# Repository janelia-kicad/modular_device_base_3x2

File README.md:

- [Repository Information](#org2d3cf65)
  - [Description](#org1d457c5)
- [Images](#orgf7fc59b)
- [Schematic](#org84fa638)
- [Gerbers](#org0e5c931)
- [Bill of Materials](#orgdca82e4)
  - [PCB Parts](#org3aed68a)
  - [Supplemental Parts](#orgb3f0c54)
  - [Vendor Parts Lists](#orgffdd84b)
- [Supplemental Documentation](#org0fd8fc3)
  - [Assembly Instructions](#org74b49ca)

# Repository Information

-   **Name:** modular\_device\_base\_3x2
-   **Version:** 1.2
-   **License:** Open-Source Hardware
-   **URL:** <https://github.com/janelia-kicad/modular_device_base_3x2>
-   **Author:** Peter Polidoro
-   **Email:** peter@polidoro.io

## Description

This board is the base of 3x2 format modular devices. It is a breakout board for the microprocessor, with connections for power, communication, and top boards.

# Images

# Schematic

[./schematic/modular\_device\_base\_3x2.pdf](./schematic/modular_device_base_3x2.pdf)

# Gerbers

Send gerbers zip file to your favorite PCB manufacturer for fabrication.

[./gerbers/modular\_device\_base\_3x2\_v1.2.zip](./gerbers/modular_device_base_3x2_v1.2.zip)

# Bill of Materials

## PCB Parts

| Item | Reference(s)         | Quantity | PartNumber          | Vendor  | Description                                           |
|---- |-------------------- |-------- |------------------- |------- |----------------------------------------------------- |
| 1    | C1 C2 C3 C4 C5       | 5        | 445-4536-1-ND       | digikey | CAP CER 10UF 50V 10% X7S 1210                         |
| 2    | C6                   | 1        | 399-13229-1-ND      | digikey | CAP CER 0.1UF 100V X7R 1210                           |
| 3    | D1 D2                | 2        | LSM115JE3/TR13CT-ND | digikey | DIODE SCHOTTKY 15V 1A DO214BA                         |
| 4    | D3 D4 D5 D6 D7 D8 D9 | 7        | 568-11697-1-ND      | digikey | DIODE SCHOTTKY 45V 10A CFP15                          |
| 5    | L1                   | 1        | 350-1712-ND         | digikey | LED 2MM 5V RT ANGLE RED PCMNT                         |
| 6    | L2                   | 1        | 350-1717-ND         | digikey | LED 2MM 5V RT ANGLE GREEN PCMNT                       |
| 7    | L3                   | 1        | 350-1719-ND         | digikey | LED 2MM 5V RT ANGLE YELLOW PCMNT                      |
| 8    | MDB1                 | 2        | S7049-ND            | digikey | 16 Position Header Through Hole Female Socket         |
| 9    | MH1 MH2 MH3 MH4      | 4        | 36-2027-ND          | digikey | Round Standoff Threaded 4-40 Aluminum 0.500in 0.187in |
| 10   | P1                   | 1        | CP-063BH-ND         | digikey | CONN PWR JACK DC 2.5X5.5 8A T/H                       |
| 11   | P2                   | 1        | ACX1655-ND          | digikey | CONN BNC JACK R/A 75 OHM PCB                          |
| 12   | P3 P5                | 2        | A100890CT-ND        | digikey | CONN HEADER 3POS R/A SMD GOLD                         |
| 13   | P4 P6                | 2        | A100903CT-ND        | digikey | CONN HEADER 2POS R/A SMD GOLD                         |
| 14   | P7                   | 1        | 732-5336-ND         | digikey | CONN HEADER 3 POS RA 2.54                             |
| 15   | P8                   | 1        | SAM10781-ND         | digikey | CONN HEADER 2POS .100in SNGL SMD                      |
| 16   | R1                   | 1        | P6.19KAACT-ND       | digikey | RES SMD 6.19K OHM 1% 1/2W 1210                        |
| 17   | REG1                 | 1        | 945-1395-5-ND       | digikey | CONV DC/DC 1A 5V OUT SIP VERT                         |
| 18   | SW1                  | 1        | CKN1860CT-ND        | digikey | SWITCH TACTILE SPST-NO 1VA 32V                        |
| 19   | TEENSY1              | 1        | 1568-1231-ND        | digikey | DEV TEENSY 3.2 13736                                  |
| 20   | U1                   | 1        | MAX6817EUT+TCT-ND   | digikey | IC DEBOUNCER SWITCH DUAL SOT23-6                      |

## Supplemental Parts

| Item | Quantity | PartNumber    | Vendor  | Description                                                              |
|---- |-------- |------------- |------- |------------------------------------------------------------------------ |
| 1    | 1        | EPS594-ND     | digikey | 30 WATT DESKTOP POWER SUPPLY 24V                                         |
| 2    | 1        | 993-1037-ND   | digikey | CORD 3COND NEMA PLUG 320-C5                                              |
| 3    | 1        | A106625CT-ND  | digikey | 14 Positions Header Unshrouded Breakaway Connector 0.100in 2 row SMD     |
| 4    | 2        | S1011EC-24-ND | digikey | 24 Positions Header Unshrouded Breakaway Connector 0.100in 1 row Through |
| 5    | 1        | S9001-ND      | digikey | CONN JUMPER SHORTING GOLD FLASH                                          |
| 6    | 1        | AE10342-ND    | digikey | CABLE USB-A TO MICRO USB-B 2M                                            |

## Vendor Parts Lists

[./bom/digikey\_parts.csv](./bom/digikey_parts.csv)

[./bom/supplemental\_digikey\_parts.csv](./bom/supplemental_digikey_parts.csv)

# Supplemental Documentation

## Assembly Instructions

-   Cut the bottom trace on the Teensy board that connects the 5V pads according to these instructions <https://www.pjrc.com/teensy/external_power.html>.
-   Solder through hole header pins into every Teensy 0.1 inch header hole.
-   Solder surface mount header pins onto the bottom of the Teensy making sure they are properly aligned.
-   Solder surface mount and through hole components onto the pcb.
-   Solder the Teensy into the pcb making sure it is properly aligned.
-   Connect header jumper to RED LED enable pins.

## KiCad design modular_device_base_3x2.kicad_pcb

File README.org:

# Created 2018-05-18 Fri 09:40
#+OPTIONS: title:nil author:nil email:nil toc:t |:t ^:nil
* Repository Information

- Name :: modular_device_base_3x2
- Version :: 1.2
- License :: Open-Source Hardware
- URL :: https://github.com/janelia-kicad/modular_device_base_3x2
- Author :: Peter Polidoro
- Email :: peter@polidoro.io

** Description

This board is the base of 3x2 format modular devices. It is a breakout board
for the microprocessor, with connections for power, communication, and top
boards.

* Images

[[file:./images/top.png]]

[[file:./images/bottom.png]]

* Schematic

[[file:./schematic/modular_device_base_3x2.pdf][./schematic/modular_device_base_3x2.pdf]]

[[file:./schematic/images/schematic00.png]]

* Gerbers

Send gerbers zip file to your favorite PCB manufacturer for fabrication.

[[file:./gerbers/modular_device_base_3x2_v1.2.zip][./gerbers/modular_device_base_3x2_v1.2.zip]]

[[file:./gerbers/images/gerbers00.png]]

[[file:./gerbers/images/gerbers01.png]]

* Bill of Materials

** PCB Parts

| Item | Reference(s)         | Quantity | PartNumber          | Vendor  | Description                                           |
|------+----------------------+----------+---------------------+---------+-------------------------------------------------------|
|    1 | C1 C2 C3 C4 C5       |        5 | 445-4536-1-ND       | digikey | CAP CER 10UF 50V 10% X7S 1210                         |
|    2 | C6                   |        1 | 399-13229-1-ND      | digikey | CAP CER 0.1UF 100V X7R 1210                           |
|    3 | D1 D2                |        2 | LSM115JE3/TR13CT-ND | digikey | DIODE SCHOTTKY 15V 1A DO214BA                         |
|    4 | D3 D4 D5 D6 D7 D8 D9 |        7 | 568-11697-1-ND      | digikey | DIODE SCHOTTKY 45V 10A CFP15                          |
|    5 | L1                   |        1 | 350-1712-ND         | digikey | LED 2MM 5V RT ANGLE RED PCMNT                         |
|    6 | L2                   |        1 | 350-1717-ND         | digikey | LED 2MM 5V RT ANGLE GREEN PCMNT                       |
|    7 | L3                   |        1 | 350-1719-ND         | digikey | LED 2MM 5V RT ANGLE YELLOW PCMNT                      |
|    8 | MDB1                 |        2 | S7049-ND            | digikey | 16 Position Header Through Hole Female Socket         |
|    9 | MH1 MH2 MH3 MH4      |        4 | 36-2027-ND          | digikey | Round Standoff Threaded 4-40 Aluminum 0.500in 0.187in |
|   10 | P1                   |        1 | CP-063BH-ND         | digikey | CONN PWR JACK DC 2.5X5.5 8A T/H                       |
|   11 | P2                   |        1 | ACX1655-ND          | digikey | CONN BNC JACK R/A 75 OHM PCB                          |
|   12 | P3 P5                |        2 | A100890CT-ND        | digikey | CONN HEADER 3POS R/A SMD GOLD                         |
|   13 | P4 P6                |        2 | A100903CT-ND        | digikey | CONN HEADER 2POS R/A SMD GOLD                         |
|   14 | P7                   |        1 | 732-5336-ND         | digikey | CONN HEADER 3 POS RA 2.54                             |
|   15 | P8                   |        1 | SAM10781-ND         | digikey | CONN HEADER 2POS .100in SNGL SMD                      |
|   16 | R1                   |        1 | P6.19KAACT-ND       | digikey | RES SMD 6.19K OHM 1% 1/2W 1210                        |
|   17 | REG1                 |        1 | 945-1395-5-ND       | digikey | CONV DC/DC 1A 5V OUT SIP VERT                         |
|   18 | SW1                  |        1 | CKN1860CT-ND        | digikey | SWITCH TACTILE SPST-NO 1VA 32V                        |
|   19 | TEENSY1              |        1 | 1568-1231-ND        | digikey | DEV TEENSY 3.2 13736                                  |
|   20 | U1                   |        1 | MAX6817EUT+TCT-ND   | digikey | IC DEBOUNCER SWITCH DUAL SOT23-6                      |

** Supplemental Parts

| Item | Quantity | PartNumber    | Vendor  | Description                                                              |
|------+----------+---------------+---------+--------------------------------------------------------------------------|
|    1 |        1 | EPS594-ND     | digikey | 30 WATT DESKTOP POWER SUPPLY 24V                                         |
|    2 |        1 | 993-1037-ND   | digikey | CORD 3COND NEMA PLUG 320-C5                                              |
|    3 |        1 | A106625CT-ND  | digikey | 14 Positions Header Unshrouded Breakaway Connector 0.100in 2 row SMD     |
|    4 |        2 | S1011EC-24-ND | digikey | 24 Positions Header Unshrouded Breakaway Connector 0.100in 1 row Through |
|    5 |        1 | S9001-ND      | digikey | CONN JUMPER SHORTING GOLD FLASH                                          |
|    6 |        1 | AE10342-ND    | digikey | CABLE USB-A TO MICRO USB-B 2M                                            |

** Vendor Parts Lists

[[file:./bom/digikey_parts.csv][./bom/digikey_parts.csv]]

[[file:./bom/supplemental_digikey_parts.csv][./bom/supplemental_digikey_parts.csv]]

* Supplemental Documentation

** Assembly Instructions

- Cut the bottom trace on the Teensy board that connects the 5V pads according
  to these instructions [[https://www.pjrc.com/teensy/external_power.html]].
- Solder through hole header pins into every Teensy 0.1 inch header hole.
- Solder surface mount header pins onto the bottom of the Teensy making sure
  they are properly aligned.
- Solder surface mount and through hole components onto the pcb.
- Solder the Teensy into the pcb making sure it is properly aligned.
- Connect header jumper to RED LED enable pins.

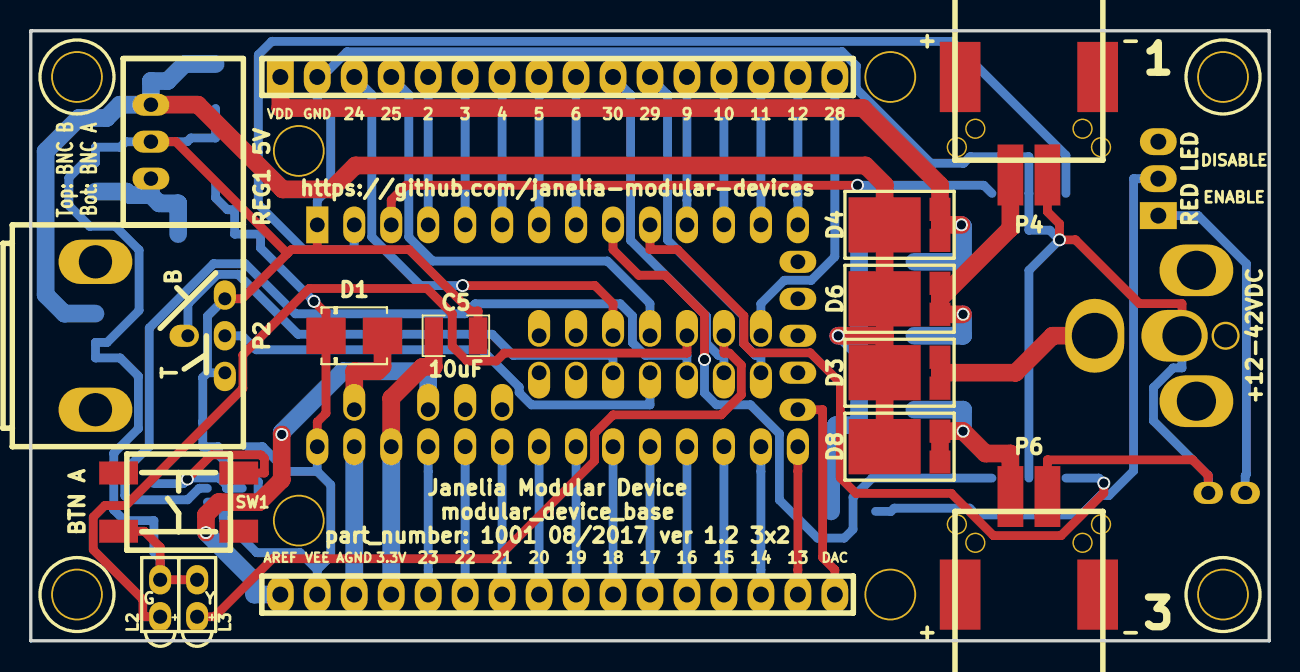
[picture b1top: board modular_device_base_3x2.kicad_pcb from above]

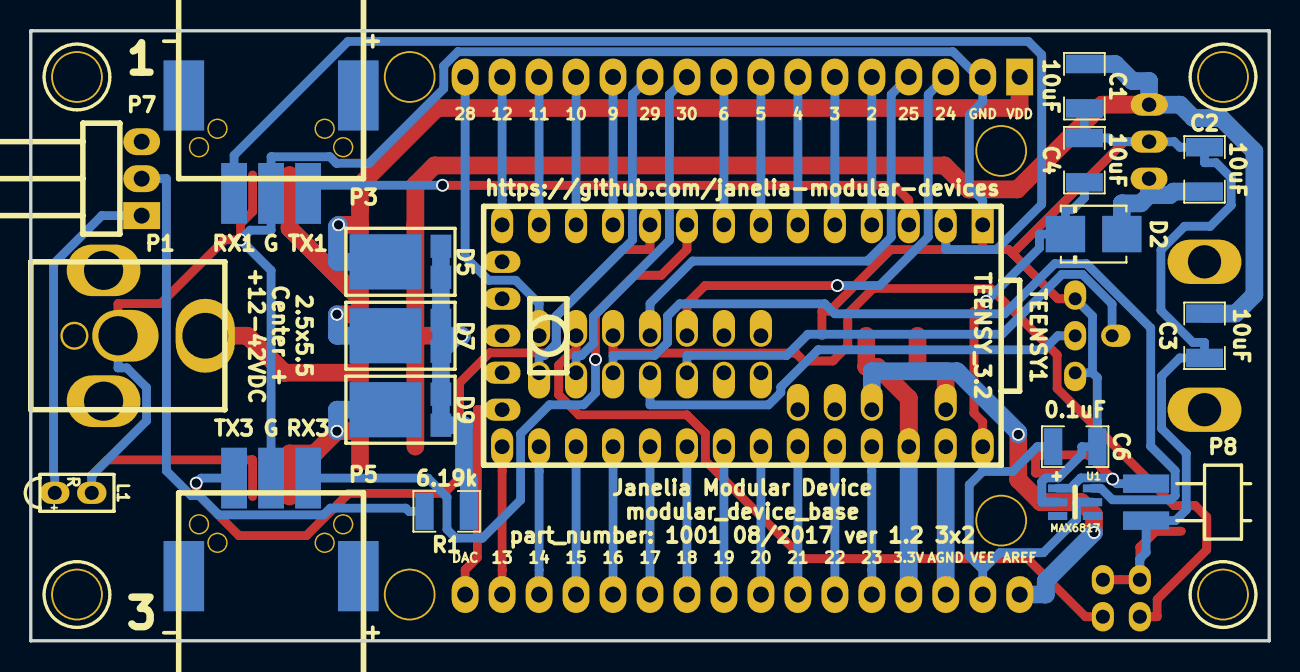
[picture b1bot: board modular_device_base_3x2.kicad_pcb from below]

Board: 2 copper layers, 85.1 x 41.9 mm, 36 parts (18 on the bottom side), 50 nets.

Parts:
C1, C2, C3, C4, C5: 10uF; SM1210
C6: 0.1uF; SM1210
D1, D2: diode_schottky_15V_1A; DO-214BA
D3, D4, D5, D6, D7, D8, D9: diode_schottky_45V_10A; CFP15
L1: LED_5V_RED_RA; LED_555-2XXX
L2: LED_5V_GRN_RA; LED_555-2XXX
L3: LED_5V_YEL_RA; LED_555-2XXX
MDB1: MODULAR_DEVICE_BASE_3x2_FEMALE; MODULAR_DEVICE_BASE_3X2_FEMALE
MH1, MH2, MH3, MH4: MNT_HOLE; MOUNTING_HOLE_4-40
P1: PWR_JACK_2.5x5.5; DCJACK_2PIN_HIGHCURRENT
P2: BNC_DOUBLE_RA; BNC_DOUBLE
P3, P5: HEADER_01X03_SMD_RA; Header_3_Pin_SMD_RA
P4, P6: HEADER_01X02_SMD_RA; Header_2_Pin_SMD_RA
P7: HEADER_01X03_RA; Header_3_Pin_RA
P8: HEADER_01X02_SMD_RA_UNSHR; Header_2_Pin_SMD_RA_UNSHR
R1: 6.19k; SM1210
REG1: CONV_DC_DC_5V_1A; DC_DC_CONV_R78C
SW1: KT_SWITCH
TEENSY1: TEENSY_3.2
U1: MAX6817

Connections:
+5V: C2.1, D2.2, REG1.3
/3V3: C5.1, MDB1.3V3, TEENSY1.3V3
/AGND: MDB1.AGND, TEENSY1.AGND
/AREF: MDB1.AREF, TEENSY1.AREF
/BNC_A: P2.1, TEENSY1.33
/BNC_B: P2.3, TEENSY1.32
/BTN_A: P8.1, SW1.2, U1.1
/BTN_A_D: TEENSY1.31, U1.6
/D2: MDB1.2, TEENSY1.2
/D3: MDB1.3, TEENSY1.3
/D4: MDB1.4, TEENSY1.4
/D5: MDB1.5, TEENSY1.5
/D6: MDB1.6, TEENSY1.6
/D9: MDB1.9, TEENSY1.9
/D10: MDB1.10, TEENSY1.10
/D11: MDB1.11, TEENSY1.11
/D12: MDB1.12, TEENSY1.12
/D13: MDB1.13, TEENSY1.13
/D14: MDB1.14, TEENSY1.14
/D15: MDB1.15, TEENSY1.15
/D16: MDB1.16, TEENSY1.16
/D17: MDB1.17, TEENSY1.17
/D18: MDB1.18, TEENSY1.18
/D19: MDB1.19, TEENSY1.19
/D20: MDB1.20, TEENSY1.20
/D21: MDB1.21, TEENSY1.21
/D22: MDB1.22, TEENSY1.22
/D23: MDB1.23, TEENSY1.23
/D24: MDB1.24, TEENSY1.24
/D25: MDB1.25, TEENSY1.25
/D28: MDB1.28, TEENSY1.28
/D29: MDB1.29, TEENSY1.29
/D30: MDB1.30, TEENSY1.30
/DAC: MDB1.DAC, TEENSY1.DAC
/LED_GRN: L2.1, TEENSY1.26
/LED_YEL: L3.1, TEENSY1.27
/RX1: P3.1, TEENSY1.0
/RX3: P5.1, TEENSY1.7
/TX1: P3.3, TEENSY1.1
/TX3: P5.3, TEENSY1.8
/V_USB: D1.2, TEENSY1.V_U
GND: C1.2, C2.2, C3.2, C4.2, C5.2, C6.2, L1.2, L2.2, L3.2, MDB1.GND, P1.2, P2.2, P2.4, P3.2, P4.2, P5.2, P6.1, P8.2, REG1.2, SW1.3, TEENSY1.GND, U1.2
unnamed: L1.1, P7.1
unnamed: P7.2, R1.2
VAA: D3.2, P1.1
VCC: D6.2, D7.1, P4.1
VDD: D4.2, D5.1, MDB1.VDD
VEE: C4.1, C6.1, D1.1, D2.1, MDB1.VEE, TEENSY1.V_IN, U1.5
VPP: C1.1, C3.1, D3.1, D4.1, D5.2, D6.1, D7.2, D8.1, D9.2, R1.1, REG1.1
VSS: D8.2, D9.1, P6.2

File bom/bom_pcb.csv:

Item,Reference(s),Value,Quantity,Description,PartNumber,Vendor
1,C1 C2 C3 C4 C5,10uF,5,CAP CER 10UF 50V 10% X7S 1210,445-4536-1-ND,digikey
2,C6,0.1uF,1,CAP CER 0.1UF 50V 10% X7R 1210,478-3586-1-ND,digikey
3,D1 D2,diode_schottky_15V_1A,2,DIODE SCHOTTKY 15V 1A DO214BA,LSM115JE3/TR13CT-ND,digikey
4,D3 D4 D5 D6 D7 D8 D9,diode_schottky_45V_10A,7,DIODE SCHOTTKY 45V 10A CFP15,568-11697-1-ND,digikey
5,L1,LED_5V_RED_RA,1,LED 2MM 5V RT ANGLE RED PCMNT,350-1712-ND,digikey
6,L2,LED_5V_GRN_RA,1,LED 2MM 5V RT ANGLE GREEN PCMNT,350-1717-ND,digikey
7,L3,LED_5V_YEL_RA,1,LED 2MM 5V RT ANGLE YELLOW PCMNT,350-1719-ND,digikey
8,MDB1,MODULAR_DEVICE_BASE_3x2_FEMALE,2,16 Position Header Through Hole Female Socket,S7049-ND,digikey
9,MH1 MH2 MH3 MH4,MNT_HOLE,4,Round Standoff Threaded 4-40 Aluminum 0.500in 0.187in,36-2027-ND,digikey
10,P1,PWR_JACK_2.5x5.5,1,CONN PWR JACK DC 2.5X5.5 8A T/H,CP-063BH-ND,digikey
11,P2,BNC_DOUBLE_RA,1,CONN BNC JACK R/A 75 OHM PCB,ACX1655-ND,digikey
12,P3 P5,HEADER_01X03_SMD_RA,2,CONN HEADER 3POS R/A SMD GOLD,A100890CT-ND,digikey
13,P4 P6,HEADER_01X02_SMD_RA,2,CONN HEADER 2POS R/A SMD GOLD,A100903CT-ND,digikey
14,P7,HEADER_01X03_RA,1,CONN HEADER 3 POS RA 2.54,732-5336-ND,digikey
15,P8,HEADER_01X02_SMD_RA_UNSHR,1,CONN HEADER 2POS .100in SNGL SMD,SAM10781-ND,digikey
16,R1,6.19k,1,RES SMD 6.19K OHM 1% 1/2W 1210,P6.19KAACT-ND,digikey
17,REG1,CONV_DC_DC_5V_1A,1,CONV DC/DC 1A 5V OUT SIP VERT,945-1395-5-ND,digikey
18,SW1,KT_SWITCH,1,SWITCH TACTILE SPST-NO 1VA 32V,CKN1860CT-ND,digikey
19,TEENSY1,TEENSY_3.2,1,DEV TEENSY 3.2 13736,1568-1231-ND,digikey
20,U1,MAX6817,1,IC DEBOUNCER SWITCH DUAL SOT23-6,MAX6817EUT+TCT-ND,digikey

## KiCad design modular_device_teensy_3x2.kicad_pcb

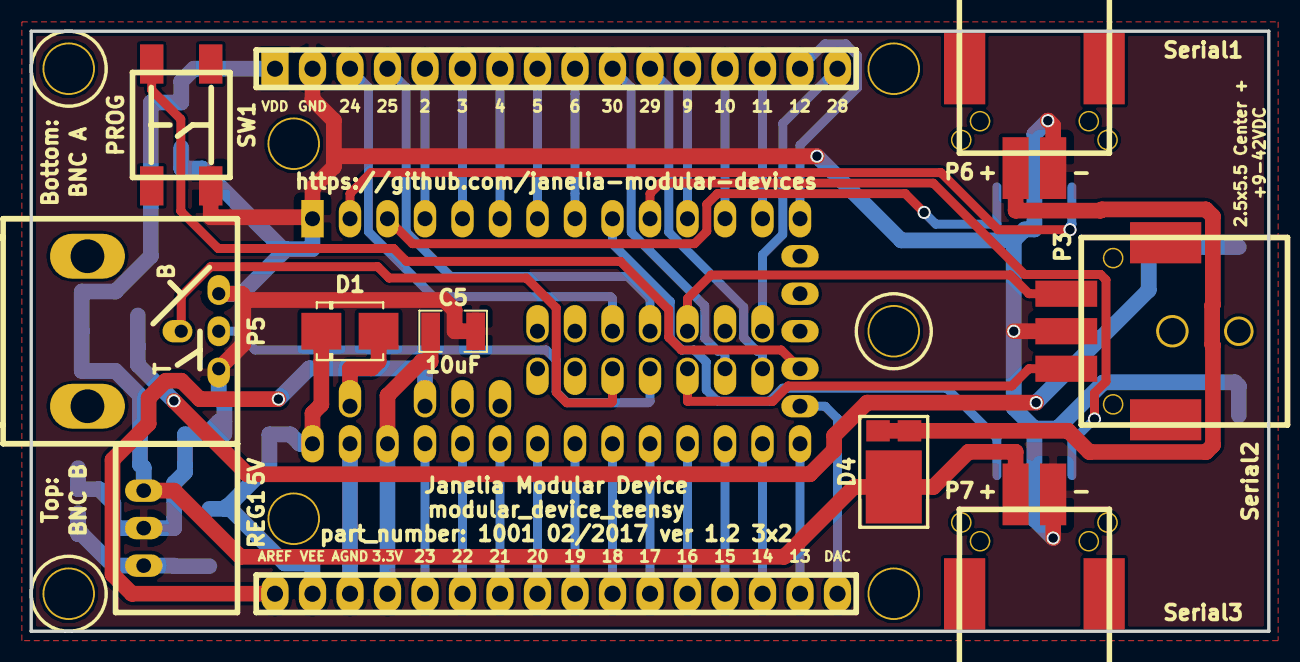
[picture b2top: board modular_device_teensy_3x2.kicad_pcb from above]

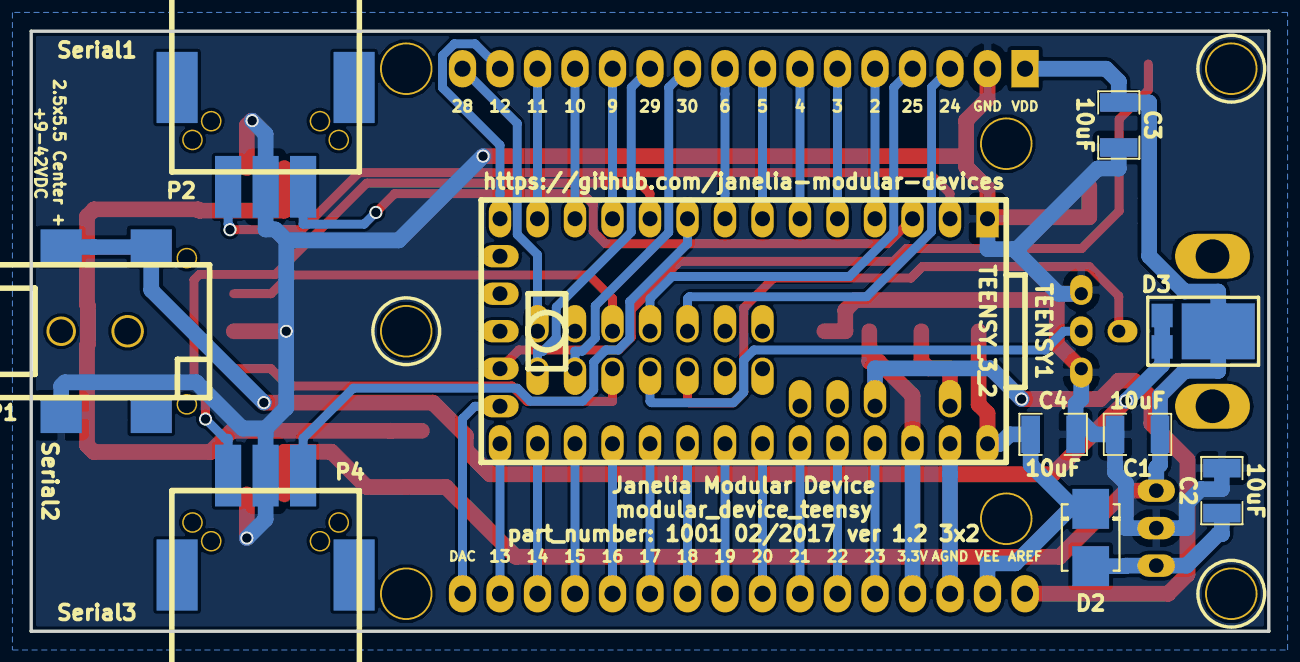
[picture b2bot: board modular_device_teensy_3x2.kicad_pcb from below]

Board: 2 copper layers, 83.8 x 40.6 mm, 23 parts (10 on the bottom side), 45 nets.

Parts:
C1, C2, C3, C4, C5: 10uF; SM1210
D1, D2: diode_schottky_15V_1A; DO-214BA
D3, D4: diode_schottky_45V_10A; CFP15
MDT1: MODULAR_DEVICE_TEENSY_3X2_FEMALE
MH1, MH2, MH3: MNT_HOLE; MOUNTING_HOLE_4-40
P1: PWR_JACK_2.5x5.5_SMD_RA; DCJACK_2PIN_HIGHCURRENT_SMD_RA
P2, P3, P4: HEADER_01X03_SMD_RA; Header_3_Pin_SMD_RA
P5: BNC_DOUBLE_RA; BNC_DOUBLE
P6, P7: HEADER_01X02_SMD_RA; Header_2_Pin_SMD_RA
REG1: CONV_DC_DC_5V_1A; DC_DC_CONV_R78C
SW1: KT_SWITCH
TEENSY1: TEENSY_3_2; TEENSY_3

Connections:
+5V: C2.1, D2.2, REG1.3
/3V3: C5.1, MDT1.3V3, TEENSY1.3V3
/AGND: MDT1.AGND, TEENSY1.AGND
/AREF: MDT1.AREF, TEENSY1.AREF
/BNC_A: P5.1, TEENSY1.33
/BNC_B: P5.3, TEENSY1.32
/D2: MDT1.2, TEENSY1.2
/D3: MDT1.3, TEENSY1.3
/D4: MDT1.4, TEENSY1.4
/D5: MDT1.5, TEENSY1.5
/D6: MDT1.6, TEENSY1.6
/D9: MDT1.9, TEENSY1.9
/D10: MDT1.10, TEENSY1.10
/D11: MDT1.11, TEENSY1.11
/D12: MDT1.12, TEENSY1.12
/D13: MDT1.13, TEENSY1.13
/D14: MDT1.14, TEENSY1.14
/D15: MDT1.15, TEENSY1.15
/D16: MDT1.16, TEENSY1.16
/D17: MDT1.17, TEENSY1.17
/D18: MDT1.18, TEENSY1.18
/D19: MDT1.19, TEENSY1.19
/D20: MDT1.20, TEENSY1.20
/D21: MDT1.21, TEENSY1.21
/D22: MDT1.22, TEENSY1.22
/D23: MDT1.23, TEENSY1.23
/D24: MDT1.24, TEENSY1.24
/D25: MDT1.25, TEENSY1.25
/D28: MDT1.28, TEENSY1.28
/D29: MDT1.29, TEENSY1.29
/D30: MDT1.30, TEENSY1.30
/DAC: MDT1.DAC, TEENSY1.DAC
/PROG: SW1.2, TEENSY1.PROG
/RX1: P2.1, TEENSY1.0
/RX2: P3.1, TEENSY1.26
/RX3: P4.1, TEENSY1.7
/TX1: P2.3, TEENSY1.1
/TX2: P3.3, TEENSY1.31
/TX3: P4.3, TEENSY1.8
/V_USB: D1.2, TEENSY1.V_U
GND: C1.2, C2.2, C3.2, C4.2, C5.2, MDT1.GND, P1.2, P2.2, P3.2, P4.2, P5.2, P5.4, P6.2, P7.1, REG1.2, SW1.3, TEENSY1.GND
VAA: D3.2, P1.1
VCC: D4.2, P6.1
VDD: C1.1, C3.1, D3.1, D4.1, MDT1.VDD, P7.2, REG1.1
VEE: C4.1, D1.1, D2.1, MDT1.VEE, TEENSY1.V_IN

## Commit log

2017-01-25 Initial commit.
2017-02-02 Silkscreen modifications.
2017-02-03 Renamed teensy -> base.
2017-02-03 modular_device_teensy -> modular_device_base.
2017-02-03 modular_device_base_3x2_v1.2.
2017-02-03 footprints: -> modular_device_base_3x2:.
2017-02-03 TEENSY_3_2 -> TEENSY_3.2.
2017-02-07 Progress towards new modifications.
2017-02-08 Finished design ver 1.0.
2017-02-08 Updated boms.
2017-03-24 Updated documentation.
2017-05-18 Added diodes and button debouncer.
2017-05-22 Progress towards v1.1.
2017-05-23 Finished v1.1.
2017-05-23 Moved components.
2017-05-24 Expanded board.
2017-05-25 Completed v1.1.
2017-05-26 Added standoffs to bom.
2017-05-26 Moved MDB_3x2 edges.
2017-08-08 Progress towards v1.2.
2017-08-09 Finished v1.2.
2017-09-13 Updated 0.1uF capacitors.
2017-09-22 Removed extra libraries.
2017-10-04 Updated LibDir.
2017-11-20 janelia-idf -> janelia-experimental-technology
2018-01-08 Updated to v4.
2018-01-08 Added v4 files.
2018-01-08 Updated to v4. Revert "Updated LibDir."
    This reverts commit ff522ac90941de1ccd4b11c52971536416c64887.
2018-01-08 Removed *cache* and *rescue*.
2018-01-08 Updated gitignore.
2018-03-09 Update license from software to hardware.
2018-04-12 README.md -> README.org.
2018-04-16 Add links to local files.
2018-04-17 Added README.md.
2018-04-17 Testing documentation changes.
2018-04-17 Automatically generate links.
2018-04-17 Try more link styles.
2018-04-19 Added .DS_Store to .gitignore.
2018-04-19 Added images.
2018-04-19 Changed image size and aspect ratio.
2018-04-19 top -> front. bottom -> back.
2018-04-20 front -> top. back -> bottom.
2018-05-16 Prepare to generate documentation.
2018-05-16 Added documentation.
2018-05-17 Updated submodules.
2018-05-17 Renamed to gerbers.pdf.
2018-05-18 Updated README.
2018-08-12 Marked extra Teensy pins.
2018-08-12 Removed v4 files.
2018-08-24 Removed F.SilkS from pads.
2018-08-27 Removed *.SilkS from pads.
2021-09-16 Update email address
2021-09-21 Remove ignored files
2022-02-22 Add guix files
2022-02-23 Add guix documentation
